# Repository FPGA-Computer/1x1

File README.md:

These are my entries to the HaD 1"x1" contest for 2015

This work is licensed under a Creative Commons BY 4.0 International License.

The full detail of this license is available at: 
http://creativecommons.org/licenses/by/4.0/

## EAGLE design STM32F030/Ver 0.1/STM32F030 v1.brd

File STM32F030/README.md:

These are my entries to the HaD 1"x1" contest for 2015

This work is licensed under a Creative Commons BY 4.0 International License.

The full detail of this license is available at: 
http://creativecommons.org/licenses/by/4.0/

Ver 0.0
Errata: J2 connector: pin 3 should be labelled as PF0 and Pin 4 should be PF1.

Ver 0.1 ("V1"):
Errate fixed and added GPIO names to the nets.  Electrically and layout is identical
to Ver 0.0.

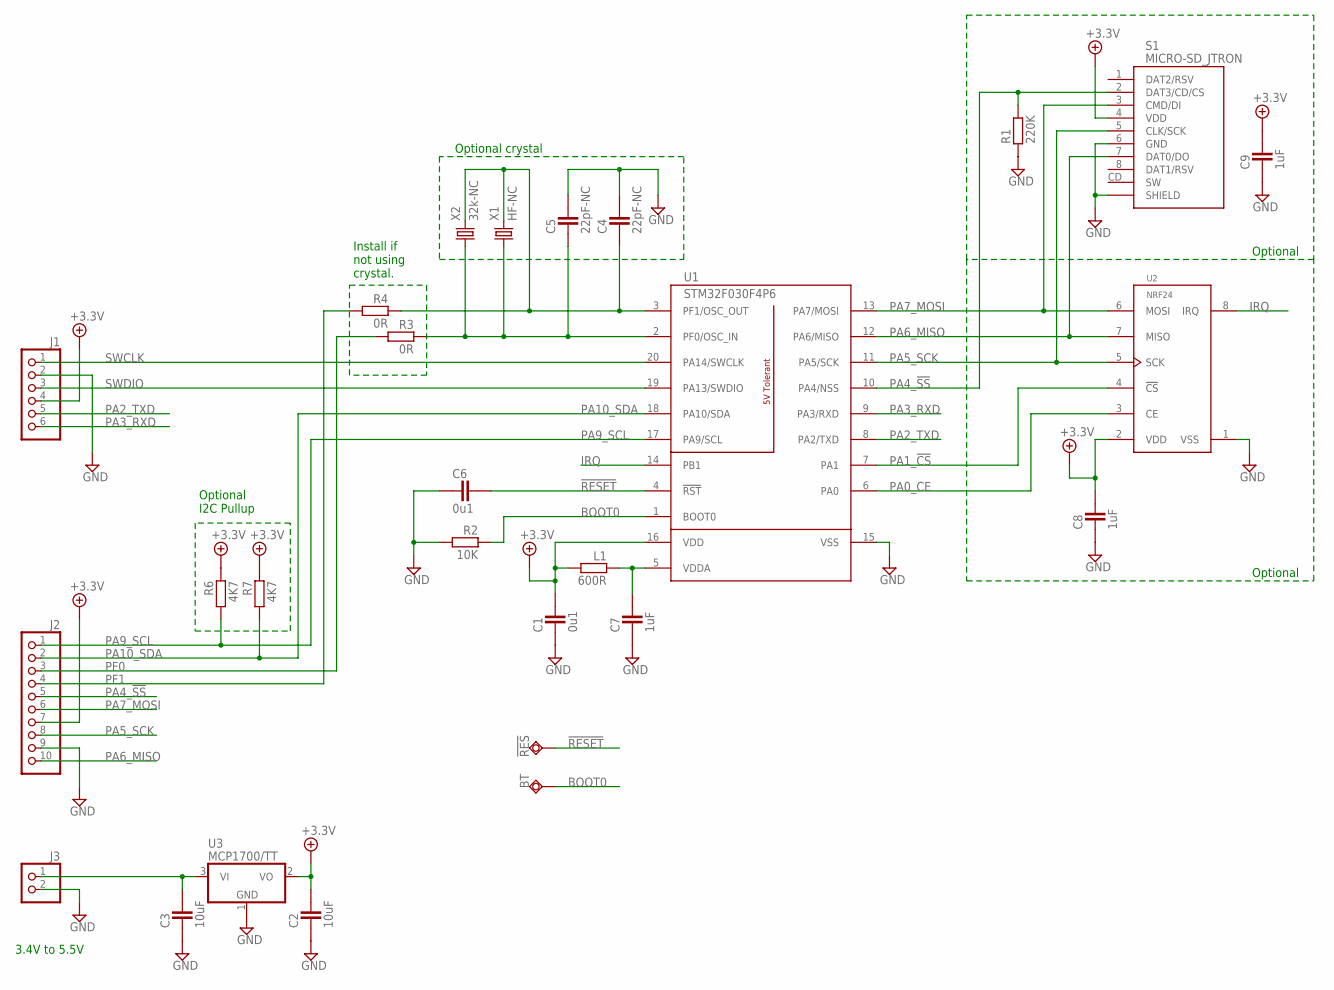
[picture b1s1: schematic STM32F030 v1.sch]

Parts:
!RES: TPSQTP08SQ; TP08SQ
BT: TPSQTP08SQ; TP08SQ
C1, C6: 0u1; CAPC1608X92N; PARTNO 0U1, 0603
C2, C3: 10uF; CAPC2012X145AN; PARTNO 10uF, 0805
C4, C5: 22pF-NC; CAPC1608X92N; PARTNO 22PF, 0603
C7, C8, C9: 1uF; CAPC1608X92N; PARTNO 1UF, 0603
J1: PINHD-1X6; 1X06; PARTNO HEADER 1X6
J2: PINHD-1X10; 1X10; PARTNO HEADER 1X10
J3: PINHD-1X2_2.54; 1X02; PARTNO HEADER 1X2
L1: 600R; RESC1608X55N; PARTNO FERRITE 0603 600R 0.2A
R1: 220K; RESC1608X55N; PARTNO 220K, 0603
R2: 10K; RESC1608X55N; PARTNO 10K, 0603
R3, R4: 0R; RESC1608X55N; PARTNO 0R, 0603
R6, R7: 4K7; RESC1608X55N; PARTNO 4K7, 0603
S1: MICRO-SD_JTRON; JTRON-MICROSD; PARTNO JTRON MICROSD SOCKET
U1: STM32F030F4P6; TSSOP20; PARTNO STM32F030F4P6
U2: NRF24; NRF24L01; PARTNO NRF24L01+ MODULE
U3: MCP1700/TT; SOT95P280X135-3N; PARTNO MCP1700T-3302E/TT
X1: HF-NC; SM49; PARTNO 12MHZ, HC49/US
X2: 32k-NC; CRYSTAL32SMT; PARTNO 32.768KHZ

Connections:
!RESET: !RES.TP, C6.2, U1.4 (!RST)
+3.3V: C1.2, C2.2, C8.2, C9.2, J1.4, J2.7, L1.2, R6.1, R7.1, S1.4 (VDD), U1.16 (VDD), U2.2 (VDD), U3.2 (VO)
BOOT0: BT.TP, R2.1, U1.1 (BOOT0)
GND: C1.1, C2.1, C3.1, C4.2, C5.2, C6.1, C7.1, C8.1, C9.1, J1.2, J2.9, J3.2, R1.1, R2.2, S1.6 (GND), S1.SHIELD@1 (SHIELD), S1.SHIELD@2 (SHIELD), S1.SHIELD@3 (SHIELD), S1.SHIELD@4 (SHIELD), U1.15 (VSS), U2.1 (VSS), U3.1 (GND)
IRQ: U1.14 (PB1), U2.8 (IRQ)
unnamed: C7.2, L1.1, U1.5 (VDDA)
unnamed: C3.2, J3.1, U3.3 (VI)
unnamed: C4.1, R4.1, U1.3 (PF1/OSC_OUT), X1.2, X2.2
unnamed: C5.1, R3.1, U1.2 (PF0/OSC_IN), X1.1, X2.1
PA0_CE: U1.6 (PA0), U2.3 (CE)
PA1_!CS: U1.7 (PA1), U2.4 (!CS)
PA2_TXD: J1.5, U1.8 (PA2/TXD)
PA3_RXD: J1.6, U1.9 (PA3/RXD)
PA4_!SS: J2.5, R1.2, S1.2 (DAT3/CD/CS), U1.10 (PA4/NSS)
PA5_SCK: J2.8, S1.5 (CLK/SCK), U1.11 (PA5/SCK), U2.5 (SCK)
PA6_MISO: J2.10, S1.7 (DAT0/DO), U1.12 (PA6/MISO), U2.7 (MISO)
PA7_MOSI: J2.6, S1.3 (CMD/DI), U1.13 (PA7/MOSI), U2.6 (MOSI)
PA9_SCL: J2.1, R6.2, U1.17 (PA9/SCL)
PA10_SDA: J2.2, R7.2, U1.18 (PA10/SDA)
PF0: J2.3, R3.2
PF1: J2.4, R4.2
SWCLK: J1.1, U1.20 (PA14/SWCLK)
SWDIO: J1.3, U1.19 (PA13/SWDIO)

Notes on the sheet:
Optional crystal
Optional
Install if not using crystal.
Optional I2C Pullup
3.4V to 5.5V

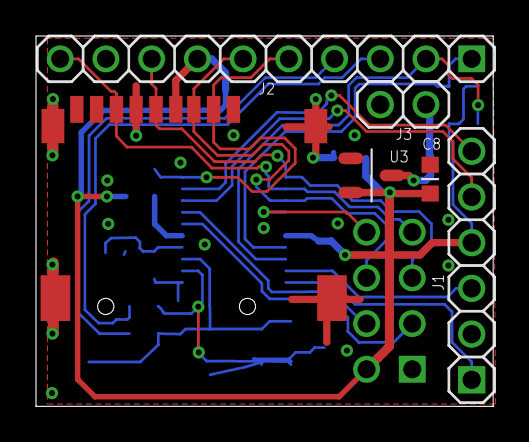
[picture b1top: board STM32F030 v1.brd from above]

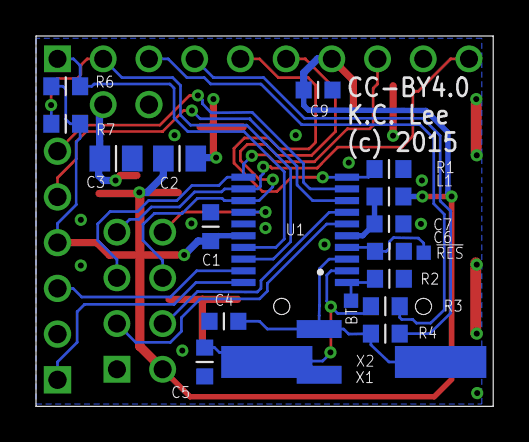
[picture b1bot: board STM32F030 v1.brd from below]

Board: 2 copper layers, 25.4 x 20.6 mm, 27 parts (20 on the bottom side), 23 nets.

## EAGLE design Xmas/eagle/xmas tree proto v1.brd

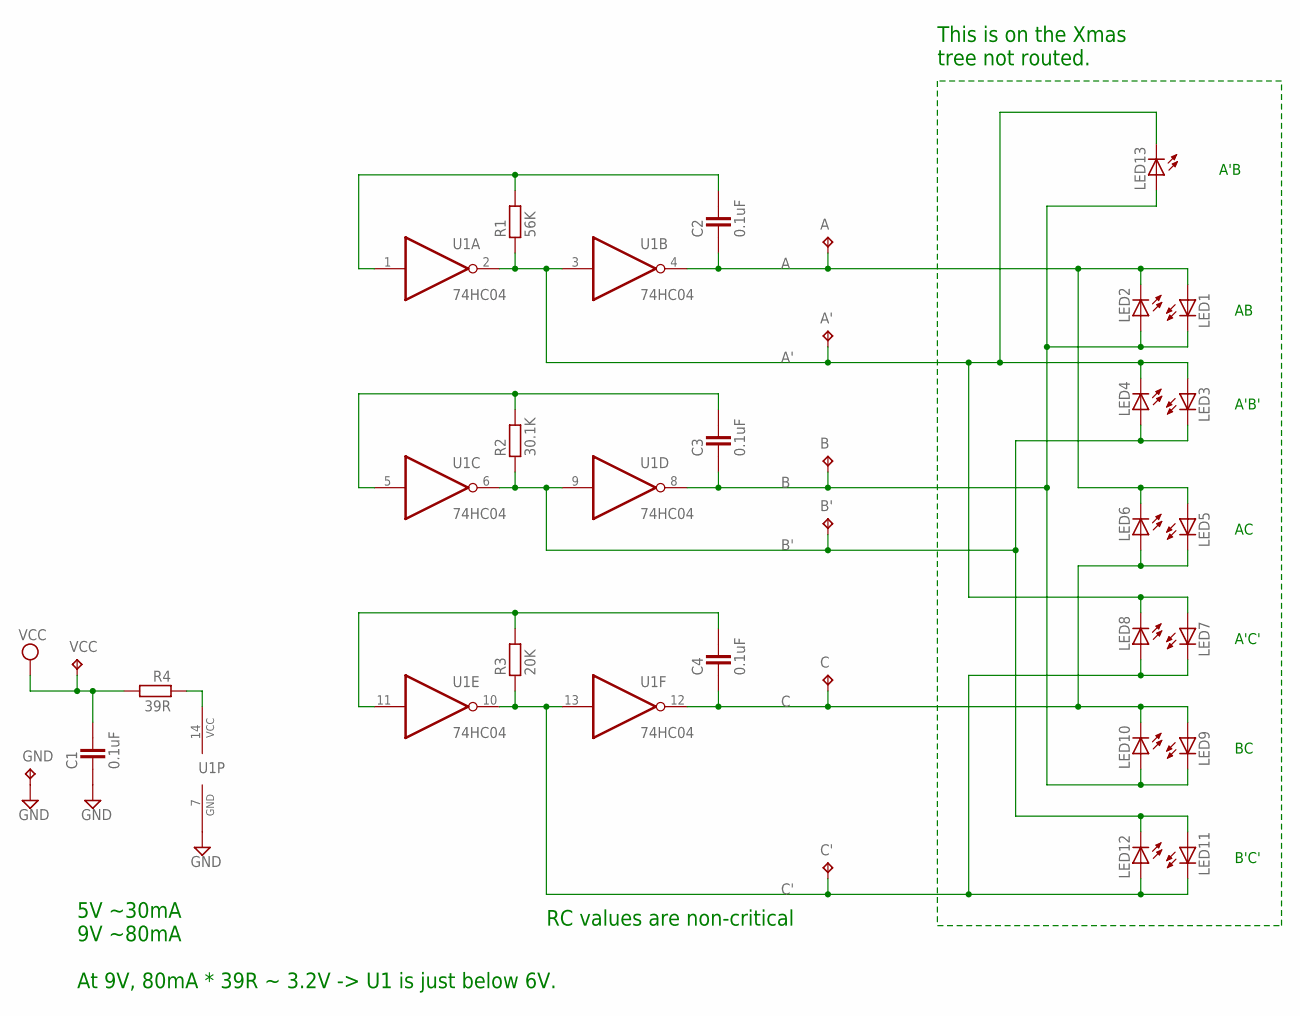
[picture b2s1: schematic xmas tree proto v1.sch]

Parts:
A: TPTP10SQ; TP10SQ
A': TPTP10SQ; TP10SQ
B: TPTP10SQ; TP10SQ
B': TPTP10SQ; TP10SQ
C: TPTP10SQ; TP10SQ
C1: 0.1uF; CAP2012X70N
C2, C3, C4: 0.1uF; CAPC1608X92N
C': TPTP10SQ; TP10SQ
GND: TPTP20SQ; TP20SQ
LED1, LED2, LED3, LED4, LED5, LED6, LED7, LED8, LED9, LED10, LED11, LED12, LED13: LED3MM
R1: 56K; RESC1608X55N
R2: 30.1K; RESC1608X55N
R3: 20K; RESC1608X55N
R4: 39R; RESC1608X55N
U1: 74HC04; SO14
VCC: TPTP20SQ; TP20SQ

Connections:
A: A.TP, C2.1, LED1.A, LED2.K (C), LED5.A, LED6.K (C), U1.4 (O)
A': A'.TP, LED3.A, LED4.K (C), LED7.A, LED8.K (C), LED13.K (C), R1.1, U1.2 (O), U1.3 (I)
B: B.TP, C3.1, LED1.K (C), LED2.A, LED9.K (C), LED10.A, LED13.A, U1.8 (O)
B': B'.TP, LED3.K (C), LED4.A, LED11.A, LED12.K (C), R2.1, U1.6 (O), U1.9 (I)
C: C.TP, C4.1, LED5.K (C), LED6.A, LED9.A, LED10.K (C), U1.12 (O)
C': C'.TP, LED7.K (C), LED8.A, LED11.K (C), LED12.A, R3.1, U1.10 (O), U1.13 (I)
GND: C1.1, GND.TP, U1.7 (GND)
unnamed: C4.2, R3.2, U1.11 (I)
unnamed: C3.2, R2.2, U1.5 (I)
unnamed: C2.2, R1.2, U1.1 (I)
unnamed: R4.1, U1.14 (VCC)
VCC: C1.2, R4.2, VCC.TP

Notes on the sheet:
RC values are non-critical
A'B'
A'C'
B'C'
A'B
5V ~30mA 9V ~80mA At 9V, 80mA * 39R ~ 3.2V -> U1 is just below 6V.
This is on the Xmas tree not routed.

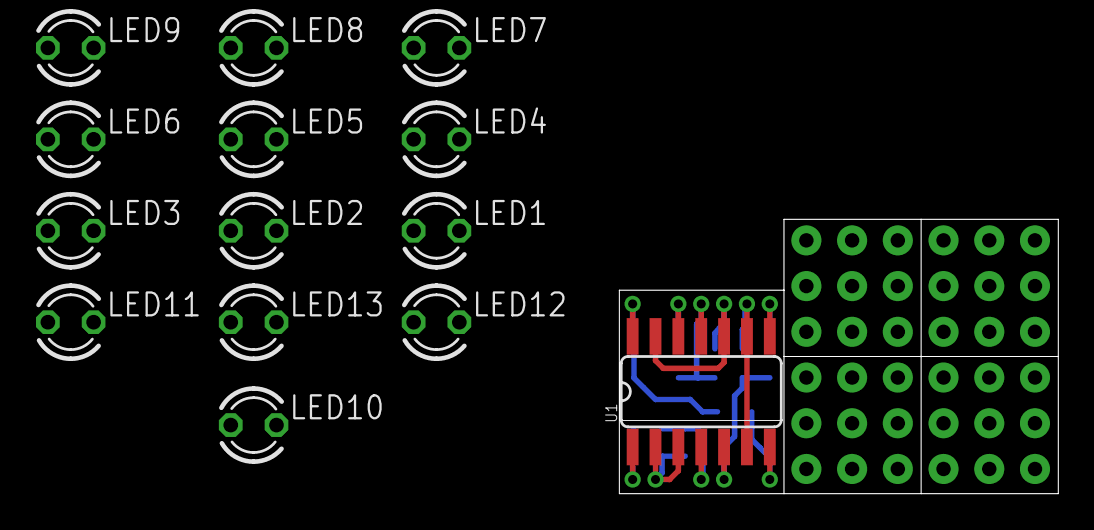
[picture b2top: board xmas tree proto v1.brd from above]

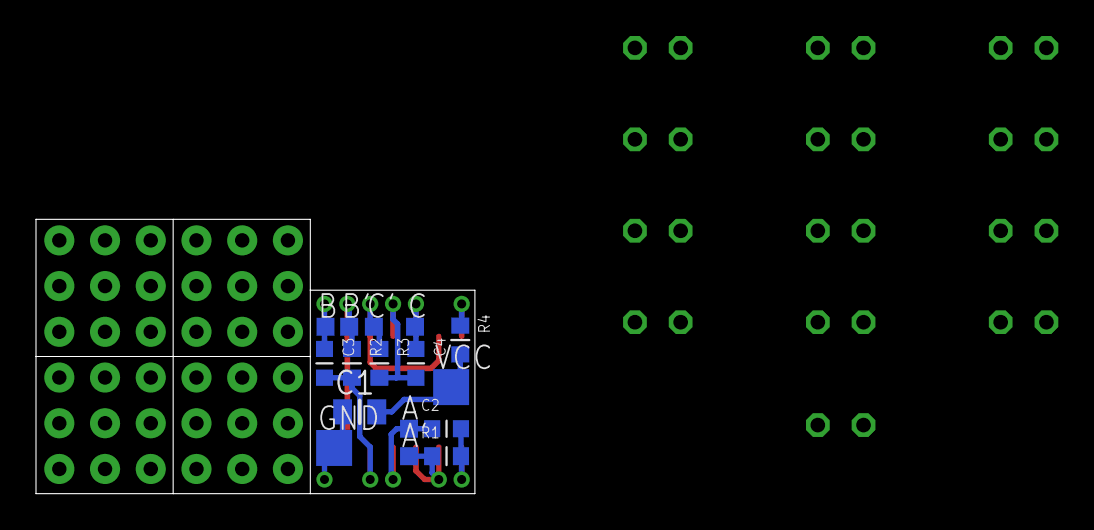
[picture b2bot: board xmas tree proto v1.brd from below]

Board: 2 copper layers, 24.4 x 15.2 mm, 30 parts (16 on the bottom side), 12 nets.

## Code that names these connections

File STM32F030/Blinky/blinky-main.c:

#include "stm32F030 iot.h"

void SystemInit(void)
{
}

void Init(void)
{
	// Default HSI: On 8MHz
	
	// GPIO default: input
	// PA13, PA14 = SWD
	
	// Enable GPIO clocks
	RCC->AHBENR |= RCC_AHBENR_GPIOAEN | RCC_AHBENR_GPIOBEN | RCC_AHBENR_GPIOFEN;
	
  // Select pin types	
	GPIOA->MODER = PIN_ALT(PA14_SWCLK)|PIN_ALT(PA13_SWDIO)|
	               PIN_OUTPUT(PA10_SDA)|PIN_OUTPUT(PA9_SCL)|
		             PIN_OUTPUT(PA7_MOSI)|PIN_OUTPUT(PA6_MISO)|
		             PIN_OUTPUT(PA5_SCK)|PIN_OUTPUT(PA4_nSS)|	
		             PIN_OUTPUT(PA3_RXD)|PIN_OUTPUT(PA2_TXD)|	
		             PIN_OUTPUT(PA1_nCS)|PIN_OUTPUT(PA0_CE);
	
	GPIOB->MODER = PIN_OUTPUT(PB1_IRQ);
	GPIOF->MODER = PIN_OUTPUT(PF1_OSC_OUT)|PIN_OUTPUT(PF0_OSC_IN);
}

void Delay(void)
{
	uint32_t i;
	
	for(i=0x1ffff;i;i--)
	  /* */;
}

void LED(uint8_t pos, uint8_t on_off)
{
	uint32_t Set_Reset;
	
	Set_Reset = on_off?0:16;
	
	switch(pos)
	{
		case 8:
		case 9:
			GPIOA->BSRR = 1<< (pos-8+PA9_SCL+Set_Reset);
			break;
		
		case 10:
			GPIOB->BSRR = 1<< (PB1_IRQ+Set_Reset);
			break;
		
		case 11:
		case 12:
			GPIOF->BSRR = 1<< (pos-11+PF0_OSC_IN+Set_Reset);
			break;
		
		default:
			if(pos<=7)
        GPIOA->BSRR = 1<< (pos + Set_Reset);
		}
}

int main(void)
{
	uint16_t i;
	
	Init();
	
	while(1)
	{	
		for(i=0;i<13;i++)
		{
			LED(i,1);
			Delay();
			LED(i,0);		
		}
	}
}

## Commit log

2015-11-17 Snapshot of OSH Park PCB order
2015-11-17 Fixed SH crystal model
2015-12-01 Update BOM
2015-12-01 Remove space in filename for URL
2015-12-02 Add gerber and CAD files
2015-12-27 clean up and clarifications - see readme.md for changes
2015-12-27 clean up net overlapped introduced in last cleanup :(

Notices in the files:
STM32F030/Ver 0.1/STM32F030 v1.brd:
CC-BY4.0
(c) 2015
